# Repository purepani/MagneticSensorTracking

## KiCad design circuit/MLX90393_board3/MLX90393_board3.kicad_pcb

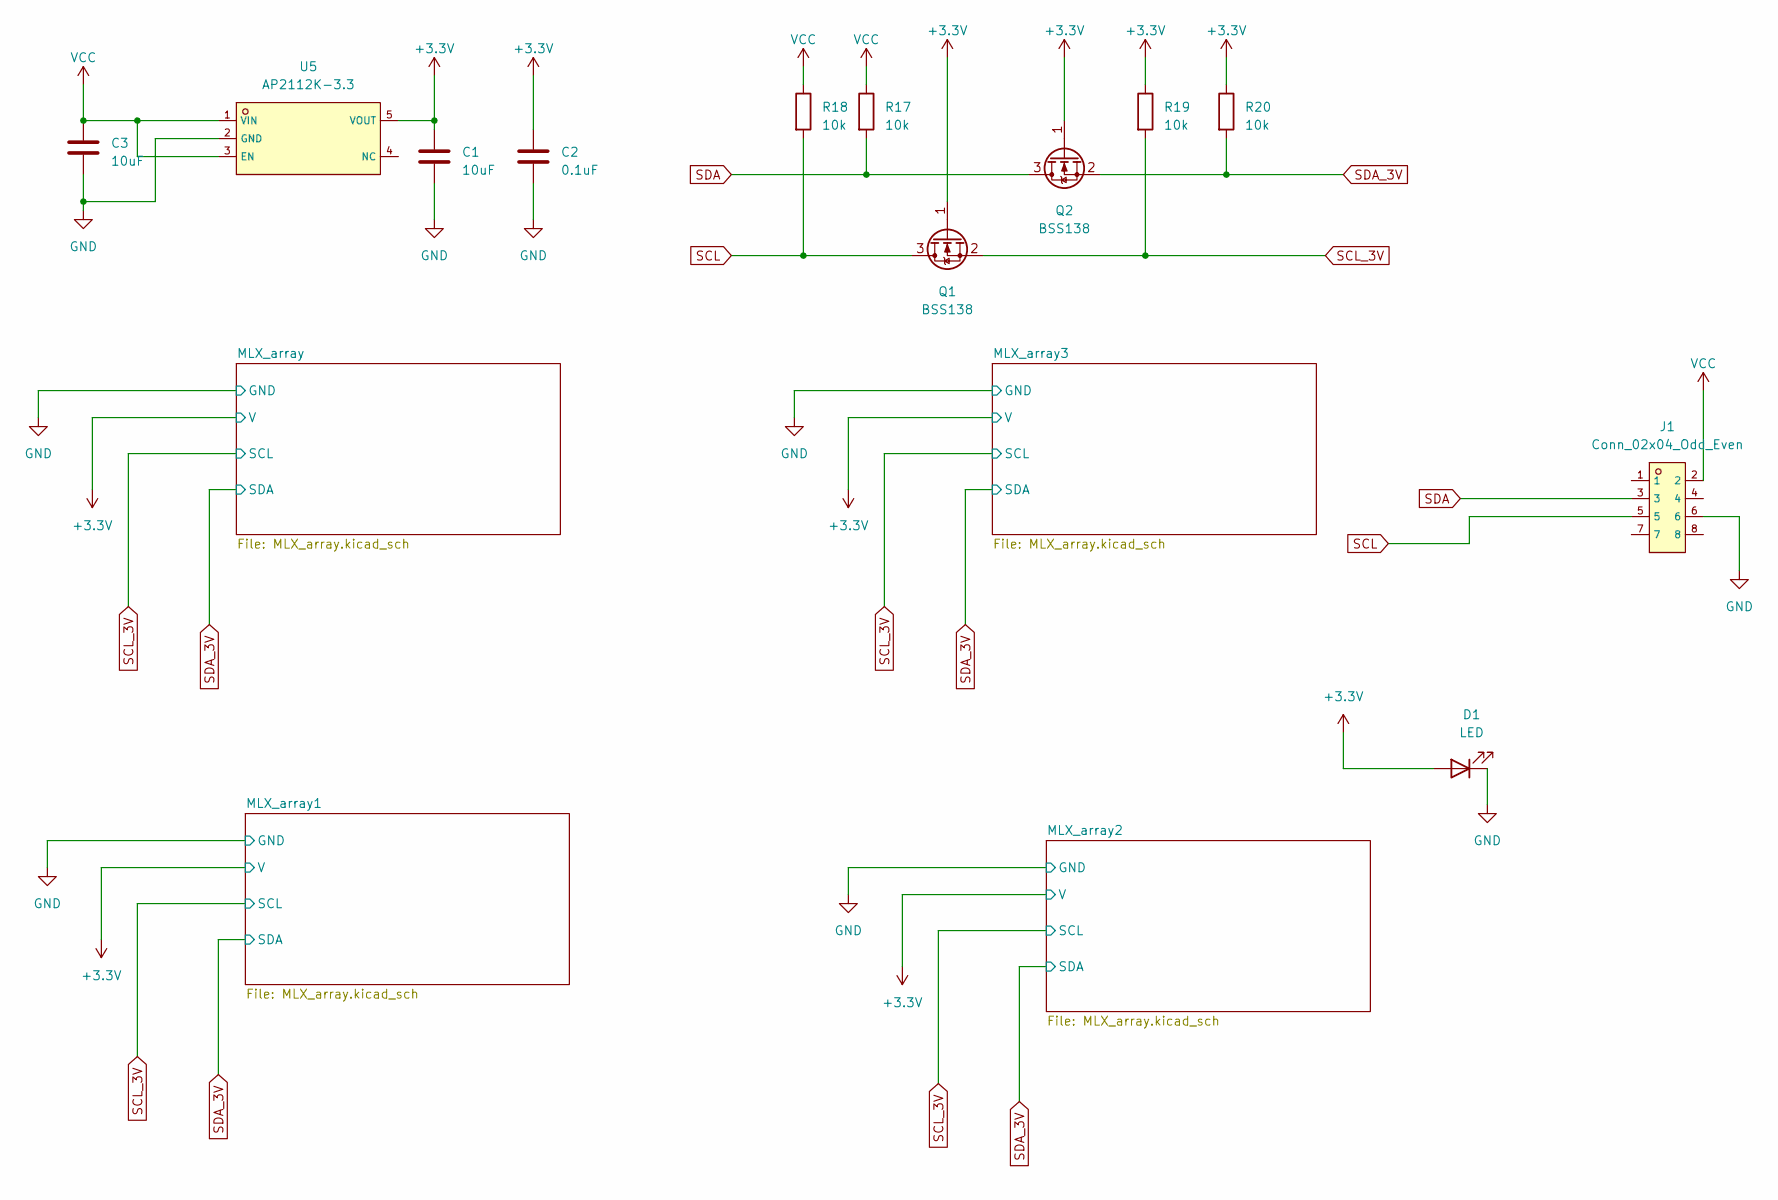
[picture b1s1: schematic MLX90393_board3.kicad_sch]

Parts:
C1, C3: 10uF; C_0603_1608Metric; LCSC C19702
C2: 0.1uF; C_0603_1608Metric; LCSC C1590
D1: LED; LED_0603_1608Metric
J1: Conn_02x04_Odd_Even; HDR-SMD_8P-P2.54-H-M-R2-C4_2; LCSC C5149354
Q1, Q2: BSS138; SOT-23; LCSC C75547
R17, R18, R19, R20: 10k; R_0603_1608Metric; LCSC C13564
U5: AP2112K-3.3; SOT-25-5_L2.9-W1.6-P0.95-LS2.8-BL; LCSC C51118

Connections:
+3.3V: C1.1, C2.1, D1.2 (A), Q1.1 (G), Q2.1 (G), R19.1, R20.1, U5.5 (VOUT); also elsewhere on the board
GND: C1.2, C2.2, C3.2, D1.1 (K), J1.6, U5.2 (GND); also elsewhere on the board
SCL: J1.5, Q1.3 (D), R18.2
SCL_3V: Q1.2 (S), R19.2; also elsewhere on the board
SDA: J1.3, Q2.3 (D), R17.2
SDA_3V: Q2.2 (S), R20.2; also elsewhere on the board
VCC: C3.1, J1.2, R17.1, R18.1, U5.1 (VIN), U5.3 (EN)

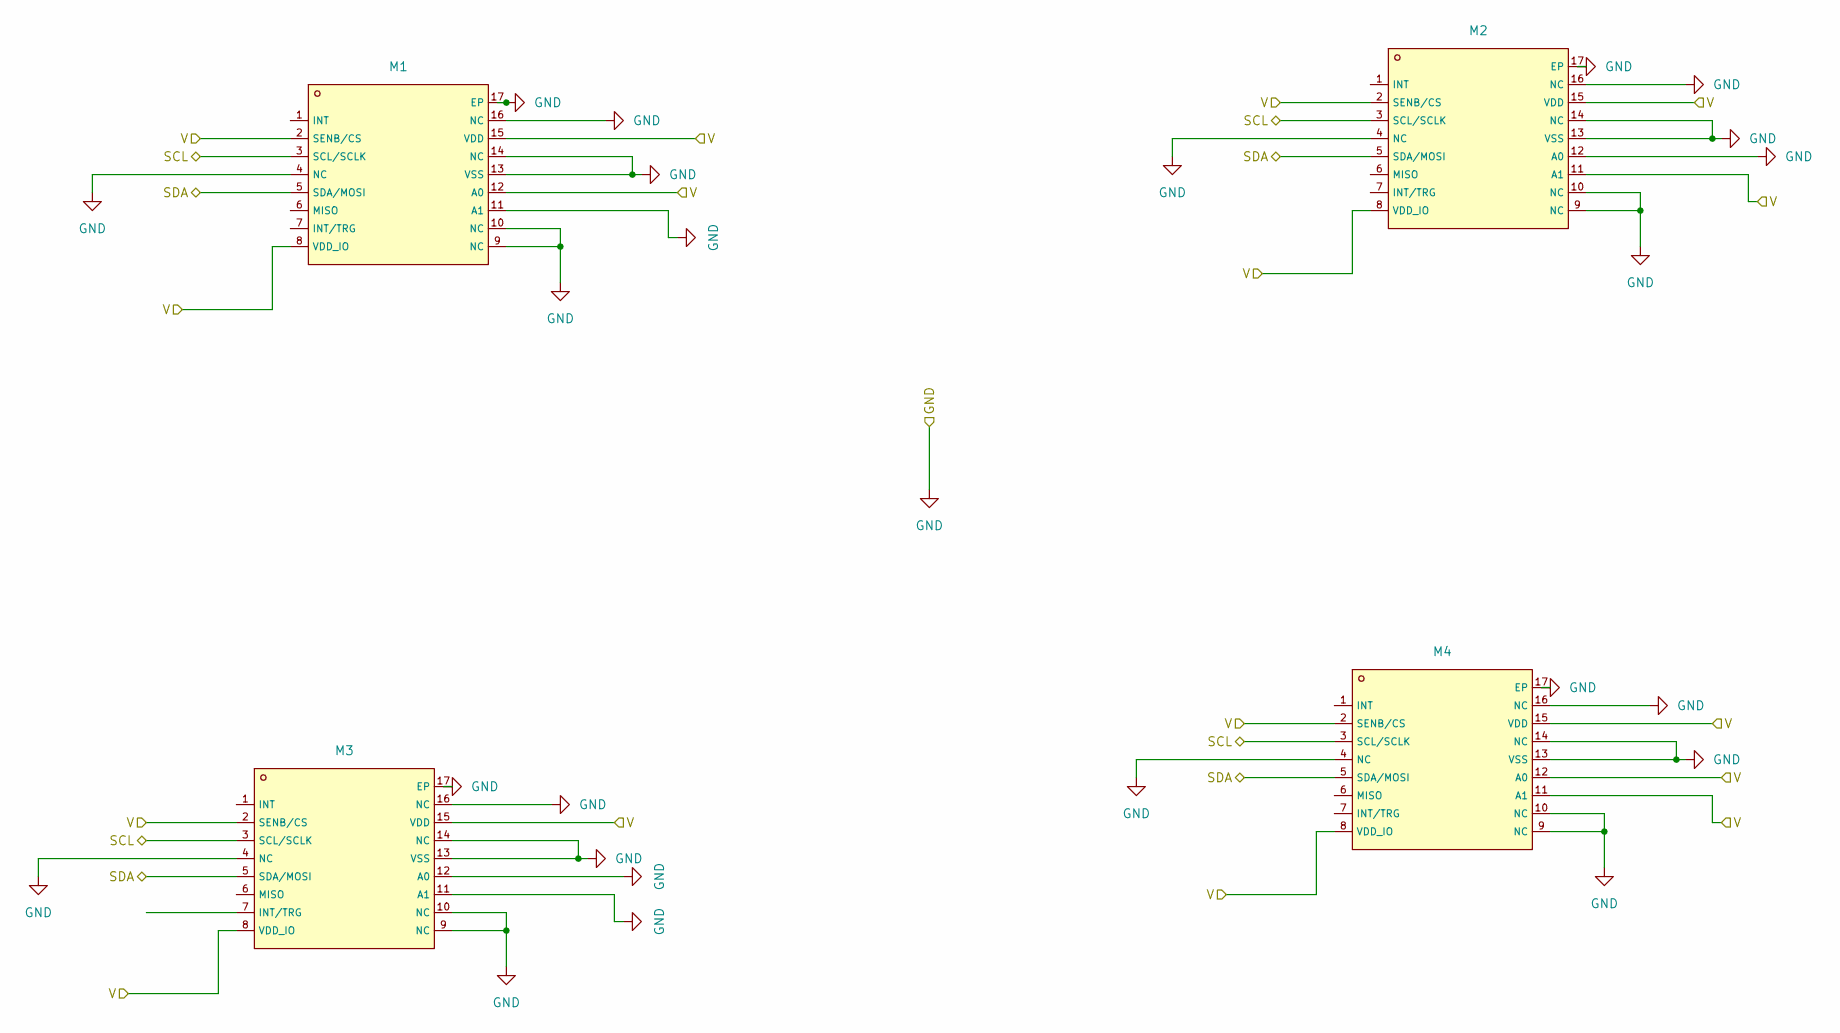
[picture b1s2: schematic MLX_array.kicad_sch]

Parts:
M1: QFN-16_L3.0-W3.0-P0.50-BL-EP1.7; LCSC C1526572
M2: QFN-16_L3.0-W3.0-P0.50-BL-EP1.7; LCSC C1526571
M3: QFN-16_L3.0-W3.0-P0.50-BL-EP1.7; LCSC C2649492
M4: QFN-16_L3.0-W3.0-P0.50-BL-EP1.7; LCSC C1526573

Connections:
+3.3V: M1.2 (SENB/CS), M1.8 (VDD_IO), M1.12 (A0), M1.15 (VDD), M2.2 (SENB/CS), M2.8 (VDD_IO), M2.11 (A1), M2.15 (VDD), M3.2 (SENB/CS), M3.8 (VDD_IO), M3.15 (VDD), M4.2 (SENB/CS), M4.8 (VDD_IO), M4.11 (A1), M4.12 (A0), M4.15 (VDD); also elsewhere on the board
GND: M1.4 (NC), M1.9 (NC), M1.10 (NC), M1.11 (A1), M1.13 (VSS), M1.14 (NC), M1.16 (NC), M1.17 (EP), M2.4 (NC), M2.9 (NC), M2.10 (NC), M2.12 (A0), M2.13 (VSS), M2.14 (NC), M2.16 (NC), M2.17 (EP), M3.4 (NC), M3.9 (NC), M3.10 (NC), M3.11 (A1), M3.12 (A0), M3.13 (VSS), M3.14 (NC), M3.16 (NC), M3.17 (EP), M4.4 (NC), M4.9 (NC), M4.10 (NC), M4.13 (VSS), M4.14 (NC), M4.16 (NC), M4.17 (EP); also elsewhere on the board
SCL_3V: M1.3 (SCL/SCLK), M2.3 (SCL/SCLK), M3.3 (SCL/SCLK), M4.3 (SCL/SCLK); also elsewhere on the board
SDA_3V: M1.5 (SDA/MOSI), M2.5 (SDA/MOSI), M3.5 (SDA/MOSI), M4.5 (SDA/MOSI); also elsewhere on the board

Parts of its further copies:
M5, M9, M13: QFN-16_L3.0-W3.0-P0.50-BL-EP1.7; LCSC C2649492
M6, M10, M14: QFN-16_L3.0-W3.0-P0.50-BL-EP1.7; LCSC C1526572
M7, M11, M15: QFN-16_L3.0-W3.0-P0.50-BL-EP1.7; LCSC C1526571
M8, M12, M16: QFN-16_L3.0-W3.0-P0.50-BL-EP1.7; LCSC C1526573

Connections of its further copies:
+3.3V: M5.2 (SENB/CS), M5.8 (VDD_IO), M5.15 (VDD), M6.2 (SENB/CS), M6.8 (VDD_IO), M6.12 (A0), M6.15 (VDD), M7.2 (SENB/CS), M7.8 (VDD_IO), M7.11 (A1), M7.15 (VDD), M8.2 (SENB/CS), M8.8 (VDD_IO), M8.11 (A1), M8.12 (A0), M8.15 (VDD), M9.2 (SENB/CS), M9.8 (VDD_IO), M9.15 (VDD), M10.2 (SENB/CS), M10.8 (VDD_IO), M10.12 (A0), M10.15 (VDD), M11.2 (SENB/CS), M11.8 (VDD_IO), M11.11 (A1), M11.15 (VDD), M12.2 (SENB/CS), M12.8 (VDD_IO), M12.11 (A1), M12.12 (A0), M12.15 (VDD), M13.2 (SENB/CS), M13.8 (VDD_IO), M13.15 (VDD), M14.2 (SENB/CS), M14.8 (VDD_IO), M14.12 (A0), M14.15 (VDD), M15.2 (SENB/CS), M15.8 (VDD_IO), M15.11 (A1), M15.15 (VDD), M16.2 (SENB/CS), M16.8 (VDD_IO), M16.11 (A1), M16.12 (A0), M16.15 (VDD); also elsewhere on the board
GND: M5.4 (NC), M5.9 (NC), M5.10 (NC), M5.11 (A1), M5.12 (A0), M5.13 (VSS), M5.14 (NC), M5.16 (NC), M5.17 (EP), M6.4 (NC), M6.9 (NC), M6.10 (NC), M6.11 (A1), M6.13 (VSS), M6.14 (NC), M6.16 (NC), M6.17 (EP), M7.4 (NC), M7.9 (NC), M7.10 (NC), M7.12 (A0), M7.13 (VSS), M7.14 (NC), M7.16 (NC), M7.17 (EP), M8.4 (NC), M8.9 (NC), M8.10 (NC), M8.13 (VSS), M8.14 (NC), M8.16 (NC), M8.17 (EP), M9.4 (NC), M9.9 (NC), M9.10 (NC), M9.11 (A1), M9.12 (A0), M9.13 (VSS), M9.14 (NC), M9.16 (NC), M9.17 (EP), M10.4 (NC), M10.9 (NC), M10.10 (NC), M10.11 (A1), M10.13 (VSS), M10.14 (NC), M10.16 (NC), M10.17 (EP), M11.4 (NC), M11.9 (NC), M11.10 (NC), M11.12 (A0), M11.13 (VSS), M11.14 (NC), M11.16 (NC), M11.17 (EP), M12.4 (NC), M12.9 (NC), M12.10 (NC), M12.13 (VSS), M12.14 (NC), M12.16 (NC), M12.17 (EP), M13.4 (NC), M13.9 (NC), M13.10 (NC), M13.11 (A1), M13.12 (A0), M13.13 (VSS), M13.14 (NC), M13.16 (NC), M13.17 (EP), M14.4 (NC), M14.9 (NC), M14.10 (NC), M14.11 (A1), M14.13 (VSS), M14.14 (NC), M14.16 (NC), M14.17 (EP), M15.4 (NC), M15.9 (NC), M15.10 (NC), M15.12 (A0), M15.13 (VSS), M15.14 (NC), M15.16 (NC), M15.17 (EP), M16.4 (NC), M16.9 (NC), M16.10 (NC), M16.13 (VSS), M16.14 (NC), M16.16 (NC), M16.17 (EP); also elsewhere on the board
SCL_3V: M5.3 (SCL/SCLK), M6.3 (SCL/SCLK), M7.3 (SCL/SCLK), M8.3 (SCL/SCLK), M9.3 (SCL/SCLK), M10.3 (SCL/SCLK), M11.3 (SCL/SCLK), M12.3 (SCL/SCLK), M13.3 (SCL/SCLK), M14.3 (SCL/SCLK), M15.3 (SCL/SCLK), M16.3 (SCL/SCLK); also elsewhere on the board
SDA_3V: M5.5 (SDA/MOSI), M6.5 (SDA/MOSI), M7.5 (SDA/MOSI), M8.5 (SDA/MOSI), M9.5 (SDA/MOSI), M10.5 (SDA/MOSI), M11.5 (SDA/MOSI), M12.5 (SDA/MOSI), M13.5 (SDA/MOSI), M14.5 (SDA/MOSI), M15.5 (SDA/MOSI), M16.5 (SDA/MOSI); also elsewhere on the board

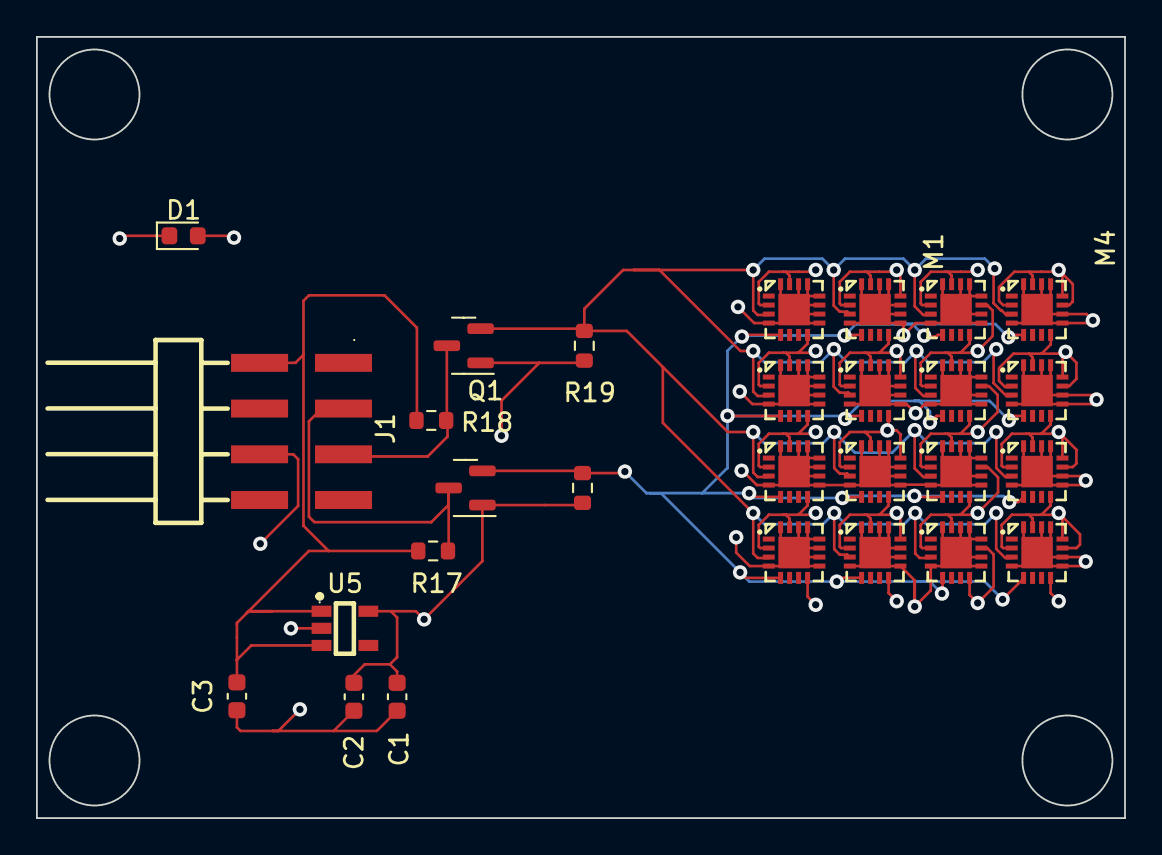
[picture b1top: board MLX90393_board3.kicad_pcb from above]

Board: 4 copper layers, 60.4 x 43.4 mm, 28 parts (0 on the bottom side), 7 nets.

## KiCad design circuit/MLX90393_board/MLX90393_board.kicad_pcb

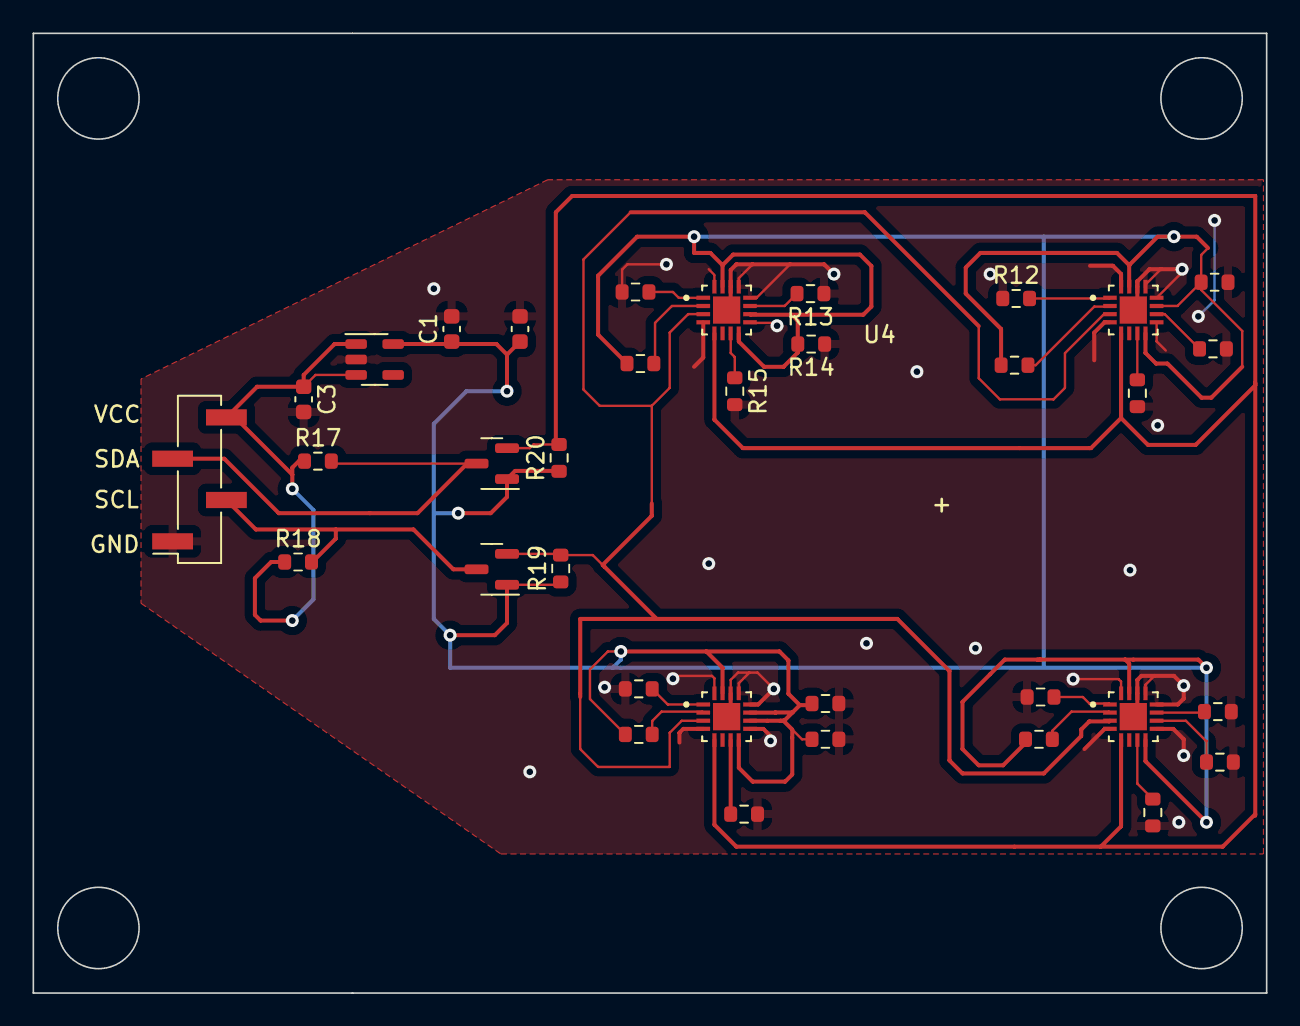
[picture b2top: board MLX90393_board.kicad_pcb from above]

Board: 2 copper layers, 75.8 x 59.0 mm, 35 parts (0 on the bottom side), 23 nets.

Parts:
C1, C3: 10uF; C_0603_1608Metric
C2: 0.1uF; C_0603_1608Metric
J1: Conn_01x04_Pin; PinHeader_1x04_P2.54mm_Vertical_SMD_Pin1Right
Q1, Q2: BSS138; SOT-23
R1, R2, R3, R4, R5, R6, R7, R8, R9, R10, R11, R12, R13, R14, R15, R16, R17, R18, R19, R20, R21, R22, R23, R24: 10k; R_0603_1608Metric
U1, U2, U3, U4: MLX90393SLW-ABA-011-SP; QFN50P300X300X100-17N
U5: AP2112K-3.3; SOT-23-5

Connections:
+3.3V: C1.1, C2.1, Q1.1 (G), Q2.1 (G), R5.2, R6.2, R9.2, R14.2, R19.1, R20.1, R21.1, R22.1, R23.1, R24.1, U1.8 (VDD_IO), U1.15 (VDD), U2.8 (VDD_IO), U2.10 (A1), U2.11 (A0), U2.15 (VDD), U3.8 (VDD_IO), U3.11 (A0), U3.15 (VDD), U4.8 (VDD_IO), U4.10 (A1), U4.15 (VDD), U5.5 (VOUT)
GND: C1.2, C2.2, C3.2, J1.1, R1.1, R2.1, R3.1, R4.2, R5.1, R6.1, R7.2, R8.1, R9.1, R10.1, R11.2, R12.1, R13.1, R14.1, R15.2, R16.1, U1.4 (NC/GND), U1.9 (NC/GND-1), U1.12 (VSS), U1.13 (NC/GND-2), U1.14 (NC/GND-3), U1.16 (NC/GND-4), U1.17 (PAD), U2.4 (NC/GND), U2.9 (NC/GND-1), U2.12 (VSS), U2.13 (NC/GND-2), U2.14 (NC/GND-3), U2.16 (NC/GND-4), U2.17 (PAD), U3.4 (NC/GND), U3.9 (NC/GND-1), U3.12 (VSS), U3.13 (NC/GND-2), U3.14 (NC/GND-3), U3.16 (NC/GND-4), U3.17 (PAD), U4.4 (NC/GND), U4.9 (NC/GND-1), U4.12 (VSS), U4.13 (NC/GND-2), U4.14 (NC/GND-3), U4.16 (NC/GND-4), U4.17 (PAD), U5.2 (GND)
unnamed: R1.2, U1.11 (A0)
unnamed: R2.2, U1.10 (A1)
unnamed: R3.2, U1.1 (INT)
unnamed: R4.1, U1.7 (INT/TRIG)
unnamed: R21.2, U1.2 (SENB/CS)
unnamed: R8.2, U2.1 (INT)
unnamed: R7.1, U2.7 (INT/TRIG)
unnamed: R24.2, U2.2 (SENB/CS)
unnamed: R10.2, U3.10 (A1)
unnamed: R12.2, U3.1 (INT)
unnamed: R11.1, U3.7 (INT/TRIG)
unnamed: R22.2, U3.2 (SENB/CS)
unnamed: R13.2, U4.11 (A0)
unnamed: R16.2, U4.1 (INT)
unnamed: R15.1, U4.7 (INT/TRIG)
unnamed: R23.2, U4.2 (SENB/CS)
SCL: J1.2, Q1.3 (D), R18.2
SCL_3V: Q1.2 (S), R19.2, U1.3 (SCL/SCLK), U2.3 (SCL/SCLK), U3.3 (SCL/SCLK), U4.3 (SCL/SCLK)
SDA: J1.3, Q2.3 (D), R17.2
SDA_3V: Q2.2 (S), R20.2, U1.5 (SDA/MOSI), U2.5 (SDA/MOSI), U3.5 (SDA/MOSI), U4.5 (SDA/MOSI)
VCC: C3.1, J1.4, R17.1, R18.1, U5.1 (VIN), U5.3 (EN)

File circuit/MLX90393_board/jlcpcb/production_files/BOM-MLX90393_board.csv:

Comment,Designator,Footprint,LCSC
10k,"R1,R10,R11,R12,R13,R14,R15,R16,R2,R21,R22,R23,R24,R3,R4,R5,R6,R7,R8,R9",R_0603_1608Metric,C13564
10k,"R17,R18,R19,R20",R_0603_1608Metric,C15401
0.1uF,C2,C_0603_1608Metric,C1590
10uF,C3,C_0603_1608Metric,C1691
10uF,C1,C_0603_1608Metric,C34696
AP2112K-3.3,U5,SOT-23-5,C51118
Conn_01x04_Pin,J1,PinHeader_1x04_P2.54mm_Vertical_SMD_Pin1Right,C5160787
MLX90393SLW-ABA-011-SP,"U1,U2,U3,U4",QFN50P300X300X100-17N,C5371633
BSS138,"Q1,Q2",SOT-23,C75547

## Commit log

2022-11-22 Adding tarfile member sanitization to extractall()
2023-04-16 Fixed DiscreteSensor
2023-04-19 done
2023-04-25 added jax and gpu support
2023-06-24 Changed Branch for data
2023-09-26 added standard
2023-10-18 Finished server
2023-10-24 added rpi camera
2023-10-25 added printer
2023-10-25 added scripts
2023-10-25 Removed pycache
2023-10-26 added camera streaming
2023-10-26 Added package changes
2023-10-26 added server script
2023-10-27 removed video support
2023-11-01 refactored socketio
2023-11-01 modified ui script
2023-11-01 Created ui factory
2023-11-02 Fixes updating position and orientation in sensor.base.SensorGroup.add_sensor
2023-11-02 Fixed camera
2023-11-02 Fixes Printer Shift
2023-11-08 Changed script ip to localhost
2023-11-08 Fixes Prusa movement
2023-11-08 Adds prediction and magnetism
2023-11-15 Adds prediction
2023-11-15 Push
2023-12-21 Adds Measurement Logging
2024-02-21 Change gitignore
2024-03-06 Adds Dynamic Modification of Sensor Settings
2024-03-06 Separates Optimization
2024-03-06 Separates Templates
2024-03-06 Adds Zeroing
2024-03-06 Fix shift
2024-03-07 Adds graph
2024-03-17 Removes video stream import
2024-03-18 Removes picamera dependency
2024-03-18 Re-enables camera
2024-04-08 Adds Temperature Compensation
2024-04-09 Begins Implementing Temperature Display
2024-04-10 renames optimization
2024-04-11 Adds temperature reporting
2024-04-11 Adds custom temperature reading code
2024-04-12 Fixes Temperature Compensation Issues
2024-04-17 Adds Data
2024-04-17 Fixes logging
2024-04-17 Updates Logs
2024-04-17 Adds More Logs
2024-04-17 Adds Updated Calibration
2024-04-18 Update Logs and adds reset logging button
2024-04-18 Update Logs
2024-12-20 added support for a second sensor board
2025-05-04 Adds uv and new circuit
2025-05-04 Setup uv workspace
2025-05-05 Change solver to library
2025-05-05 Remove old circuit that causes windows issues
2025-05-09 Remove temp files and fix gitignore
